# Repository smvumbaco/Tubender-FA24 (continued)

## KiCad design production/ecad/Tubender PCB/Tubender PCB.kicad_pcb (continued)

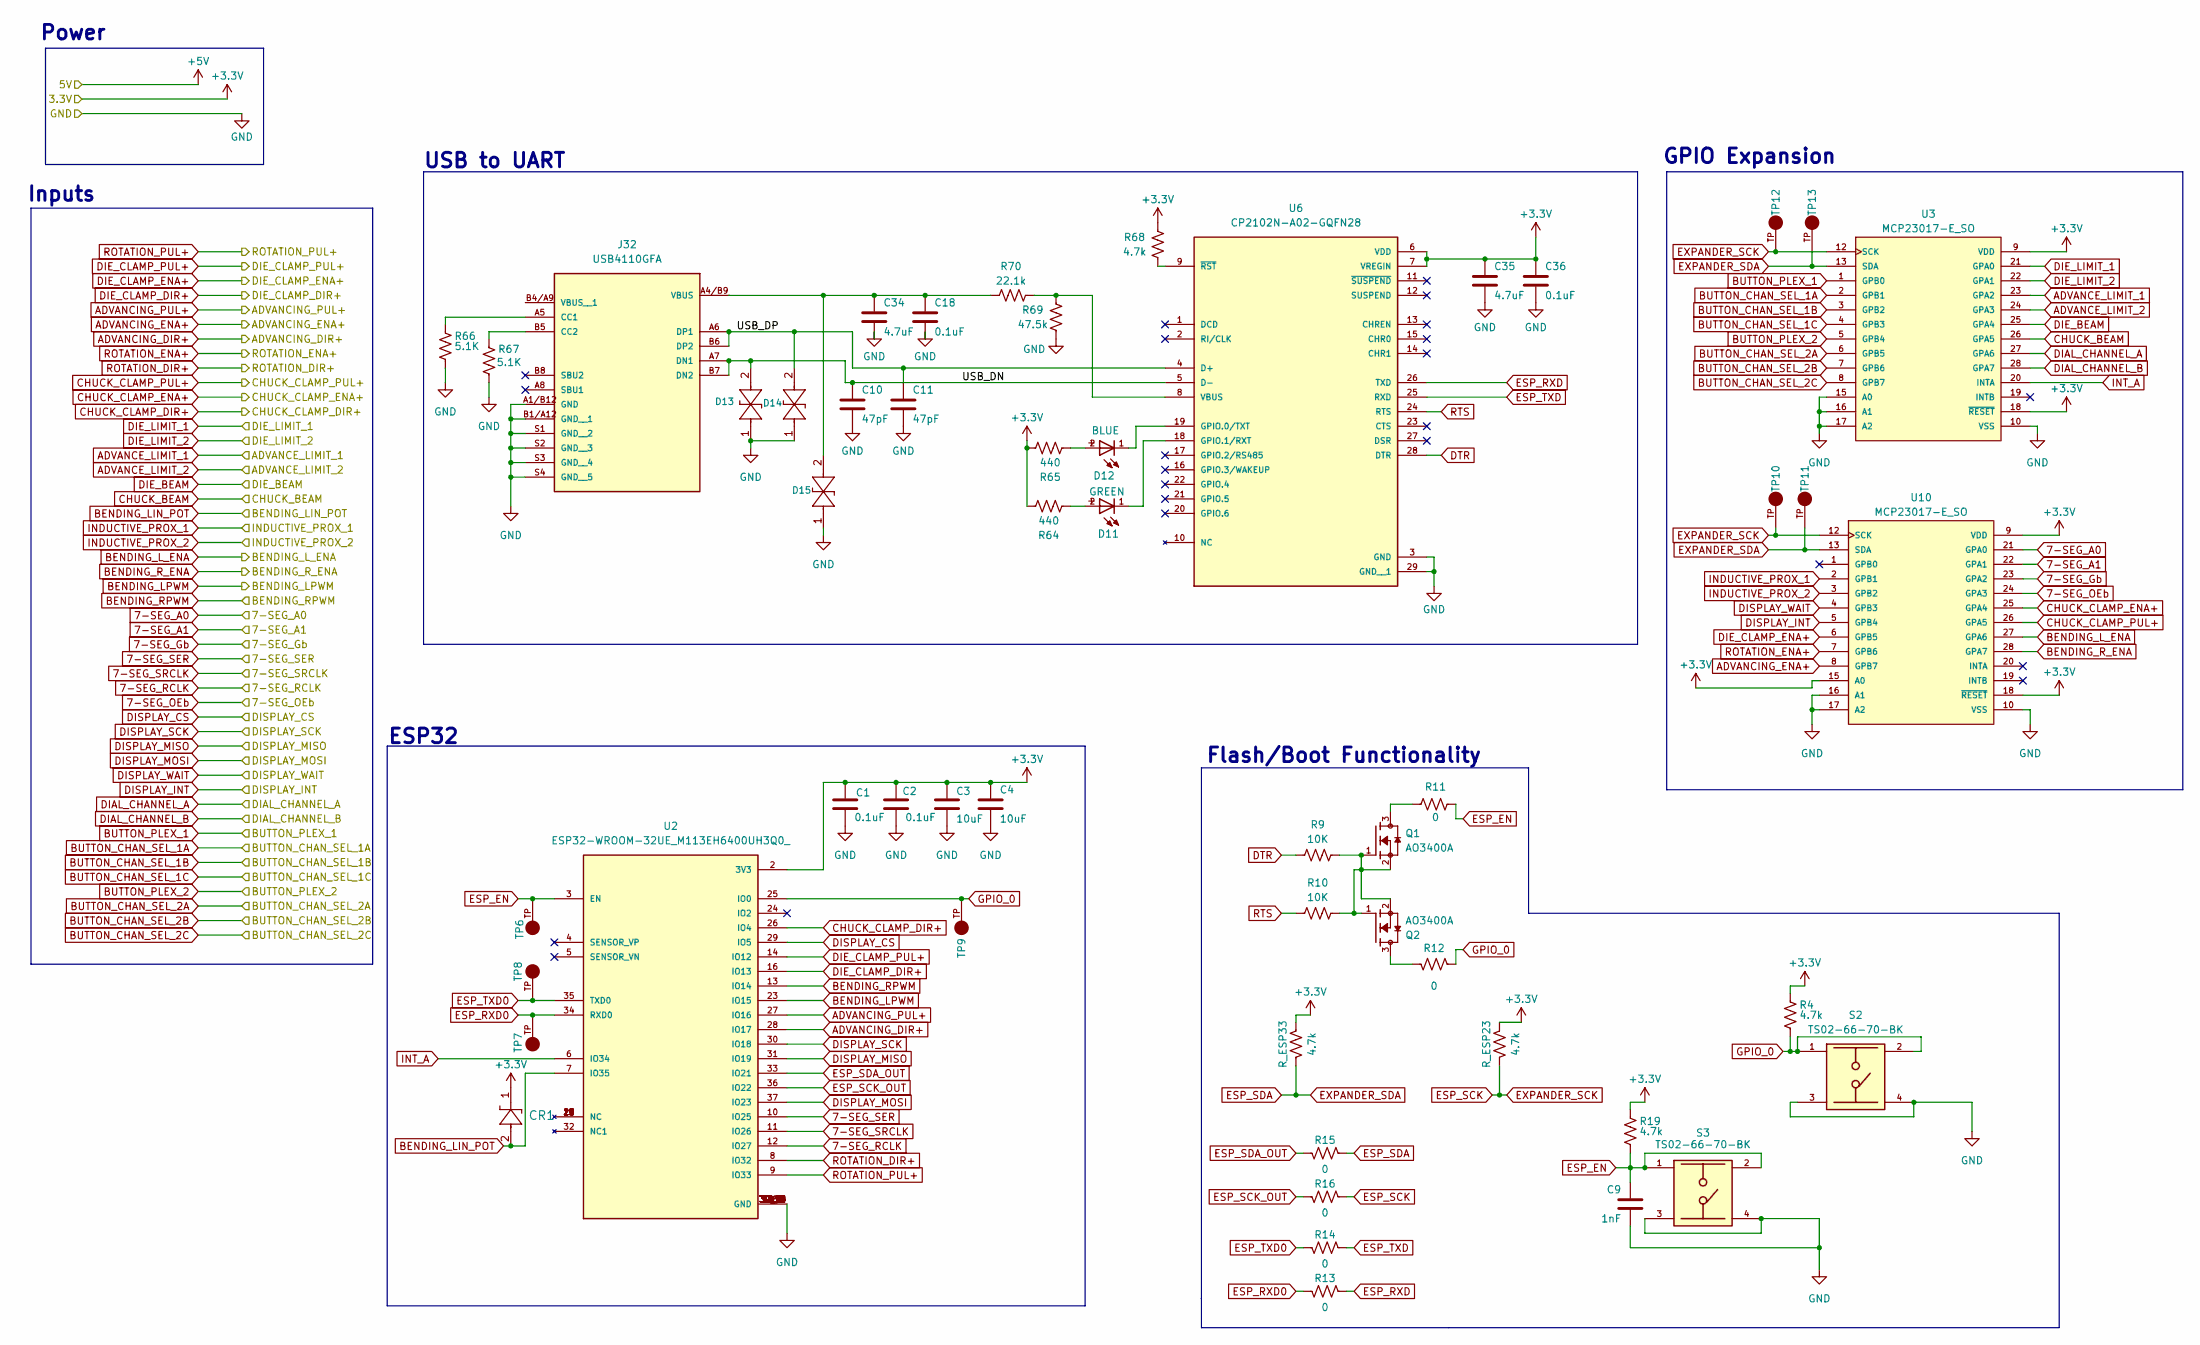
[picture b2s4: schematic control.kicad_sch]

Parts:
C1, C2, C18, C36: 0.1uF; C_0805_2012Metric
C3, C4: 10uF; C_0805_2012Metric
C9: 1nF; C_0805_2012Metric
C10, C11: 47pF; C_0805_2012Metric
C34, C35: 4.7uF; C_0805_2012Metric
CR1: PMEG4010CEH; SOD123F_NXP
D11: GREEN; WL-SMCW_0603
D12: BLUE; WL-SMCW_0603
D13, D14, D15: RCLAMP1521P.TCT; TVS_DFN2_SLP1006P2_SEM
J32: USB4110GFA; GCT_USB4110GFA
Q1, Q2: AO3400A; SOT95P280X125-3N; PARTREV L
R4, R19, R68: 4.7k; R_0805_2012Metric
R9, R10: 10K; R_0805_2012Metric
R11, R12, R13, R14, R15, R16: 0; R_0805_2012Metric
R64, R65: 440; R_0805_2012Metric
R66, R67: 5.1K; R_0805_2012Metric
R69: 47.5k; R_0805_2012Metric
R70: 22.1k; R_0805_2012Metric
R_ESP23, R_ESP33: 4.7k; R_0805_2012Metric
S2, S3: TS02-66-70-BK; SW_TS02-66-70-BK-260-LCR-D; PARTREV 1.0
TP6, TP7, TP8, TP9, TP10, TP11, TP12, TP13: 5006; KEYSTONE_5006; PARTREV F
U2: ESP32-WROOM-32UE_M113EH6400UH3Q0_; MODULE_ESP32-WROOM-32UE_M113EH6400UH3Q0_; PARTREV 1.2
U3, U10: MCP23017-E_SO; SOIC127P1030X265-28N; PARTREV C
U6: CP2102N-A02-GQFN28; QFN50P500X500X80-29N; PARTREV 1.5

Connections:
3.3V: C1.1, C2.1, C3.1, C4.1, C35.1, C36.1, CR1.1, R4.2, R19.2, R64.2, R65.2, R68.2, R_ESP23.2, R_ESP33.2, U2.2 (3V3), U3.9 (VDD), U3.18 (~RESET), U6.6 (VDD), U6.7 (VREGIN), U10.9 (VDD), U10.15 (A0), U10.18 (~RESET); also elsewhere on the board
7-SEG_A0: U10.21 (GPA0); also elsewhere on the board
7-SEG_A1: U10.22 (GPA1); also elsewhere on the board
7-SEG_Gb: U10.23 (GPA2); also elsewhere on the board
7-SEG_OEb: U10.24 (GPA3); also elsewhere on the board
7-SEG_RCLK: U2.12 (IO27); also elsewhere on the board
7-SEG_SER: U2.10 (IO25); also elsewhere on the board
7-SEG_SRCLK: U2.11 (IO26); also elsewhere on the board
/CONTROL/USB_DN: C10.1, D13.2, J32.A7 (DN1), J32.B7 (DN2), U6.5 (D-)
/CONTROL/USB_DP: C11.1, D14.2, J32.A6 (DP1), J32.B6 (DP2), U6.4 (D+)
ADVANCE_LIMIT_1: U3.23 (GPA2); also elsewhere on the board
ADVANCE_LIMIT_2: U3.24 (GPA3); also elsewhere on the board
ADVANCING_DIR+: U2.28 (IO17); also elsewhere on the board
ADVANCING_ENA+: U10.8 (GPB7); also elsewhere on the board
ADVANCING_PUL+: U2.27 (IO16); also elsewhere on the board
BENDING_LIN_POT: CR1.2, U2.7 (IO35); also elsewhere on the board
BENDING_LPWM: U2.23 (IO15); also elsewhere on the board
BENDING_L_ENA: U10.27 (GPA6); also elsewhere on the board
BENDING_RPWM: U2.13 (IO14); also elsewhere on the board
BENDING_R_ENA: U10.28 (GPA7); also elsewhere on the board
BUTTON_CHAN_SEL_1A: U3.2 (GPB1); also elsewhere on the board
BUTTON_CHAN_SEL_1B: U3.3 (GPB2); also elsewhere on the board
BUTTON_CHAN_SEL_1C: U3.4 (GPB3); also elsewhere on the board
BUTTON_CHAN_SEL_2A: U3.6 (GPB5); also elsewhere on the board
BUTTON_CHAN_SEL_2B: U3.7 (GPB6); also elsewhere on the board
BUTTON_CHAN_SEL_2C: U3.8 (GPB7); also elsewhere on the board
BUTTON_PLEX_1: U3.1 (GPB0); also elsewhere on the board
BUTTON_PLEX_2: U3.5 (GPB4); also elsewhere on the board
CHUCK_BEAM: U3.26 (GPA5); also elsewhere on the board
CHUCK_CLAMP_DIR+: U2.26 (IO4); also elsewhere on the board
CHUCK_CLAMP_ENA+: U10.25 (GPA4); also elsewhere on the board
CHUCK_CLAMP_PUL+: U10.26 (GPA5); also elsewhere on the board
DIAL_CHANNEL_A: U3.27 (GPA6); also elsewhere on the board
DIAL_CHANNEL_B: U3.28 (GPA7); also elsewhere on the board
DIE_BEAM: U3.25 (GPA4); also elsewhere on the board
DIE_CLAMP_DIR+: U2.16 (IO13); also elsewhere on the board
DIE_CLAMP_ENA+: U10.6 (GPB5); also elsewhere on the board
DIE_CLAMP_PUL+: U2.14 (IO12); also elsewhere on the board
DIE_LIMIT_1: U3.21 (GPA0); also elsewhere on the board
DIE_LIMIT_2: U3.22 (GPA1); also elsewhere on the board
DISPLAY_CS: U2.29 (IO5); also elsewhere on the board
DISPLAY_INT: U10.5 (GPB4); also elsewhere on the board
DISPLAY_MISO: U2.31 (IO19); also elsewhere on the board
DISPLAY_MOSI: U2.37 (IO23); also elsewhere on the board
DISPLAY_SCK: U2.30 (IO18); also elsewhere on the board
DISPLAY_WAIT: U10.4 (GPB3); also elsewhere on the board
DTR: R9.1, U6.28 (DTR)
ESP_EN: C9.1, R11.2, R19.1, S3.1, S3.2, TP6.TP, U2.3 (EN)
ESP_RXD: R13.2, U6.26 (TXD)
ESP_RXD0: R13.1, TP7.TP, U2.34 (RXD0)
ESP_SCK: R16.2, R_ESP23.1, TP10.TP, TP12.TP, U3.12 (SCK), U10.12 (SCK)
ESP_SCK_OUT: R16.1, U2.36 (IO22)
ESP_SDA: R15.2, R_ESP33.1, TP11.TP, TP13.TP, U3.13 (SDA), U10.13 (SDA)
ESP_SDA_OUT: R15.1, U2.33 (IO21)
ESP_TXD: R14.2, U6.25 (RXD)
ESP_TXD0: R14.1, TP8.TP, U2.35 (TXD0)
GND: C1.2, C2.2, C3.2, C4.2, C9.2, C10.2, C11.2, C18.2, C34.2, C35.2, C36.2, D13.1, D14.1, D15.1, J32.A1/B12 (GND), J32.B1/A12 (GND__1), J32.S1 (GND__2), J32.S2 (GND__3), J32.S3 (GND__4), J32.S4 (GND__5), R66.1, R67.1, R69.1, S2.3, S2.4, S3.3, S3.4, U2.1 (GND), U2.15 (GND), U2.38 (GND), U2.39_1 (GND), U2.39_2 (GND), U2.39_3 (GND), U2.39_4 (GND), U2.39_5 (GND), U2.39_6 (GND), U2.39_7 (GND), U2.39_8 (GND), U2.39_9 (GND), U2.39_10 (GND), U2.39_11 (GND), U2.39_12 (GND), U2.39_13 (GND), U2.39_14 (GND), U2.39_15 (GND), U2.39_16 (GND), U2.39_17 (GND), U2.39_18 (GND), U2.39_19 (GND), U2.39_20 (GND), U2.39_21 (GND), U3.10 (VSS), U3.15 (A0), U3.16 (A1), U3.17 (A2), U6.3 (GND), U6.29 (GND__1), U10.10 (VSS), U10.16 (A1), U10.17 (A2); also elsewhere on the board
GPIO_0: R4.1, R12.2, S2.1, S2.2, TP9.TP, U2.25 (IO0)
INDUCTIVE_PROX_1: U10.2 (GPB1); also elsewhere on the board
INDUCTIVE_PROX_2: U10.3 (GPB2); also elsewhere on the board
INT_A: U2.6 (IO34), U3.20 (INTA)
unnamed: D11.2, R64.1
unnamed: D12.2, R65.1
unnamed: J32.A5 (CC1), R66.2
unnamed: J32.B5 (CC2), R67.2
unnamed: C18.1, C34.1, D15.2, J32.A4/B9 (VBUS), R70.1
unnamed: Q1.1, Q1.2, Q2.1, Q2.2, R9.2, R10.2
unnamed: Q1.3, R11.1
unnamed: Q2.3, R12.1
unnamed: D12.1, U6.19 (GPIO.0/TXT)
unnamed: D11.1, U6.18 (GPIO.1/RXT)
unnamed: R69.2, R70.2, U6.8 (VBUS)
unnamed: R68.1, U6.9 (~RST)
ROTATION_DIR+: U2.8 (IO32); also elsewhere on the board
ROTATION_ENA+: U10.7 (GPB6); also elsewhere on the board
ROTATION_PUL+: U2.9 (IO33); also elsewhere on the board
RTS: R10.1, U6.24 (RTS)

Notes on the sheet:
USB to UART
GPIO Expansion
Inputs
ESP32
Power
Flash/Boot Functionality

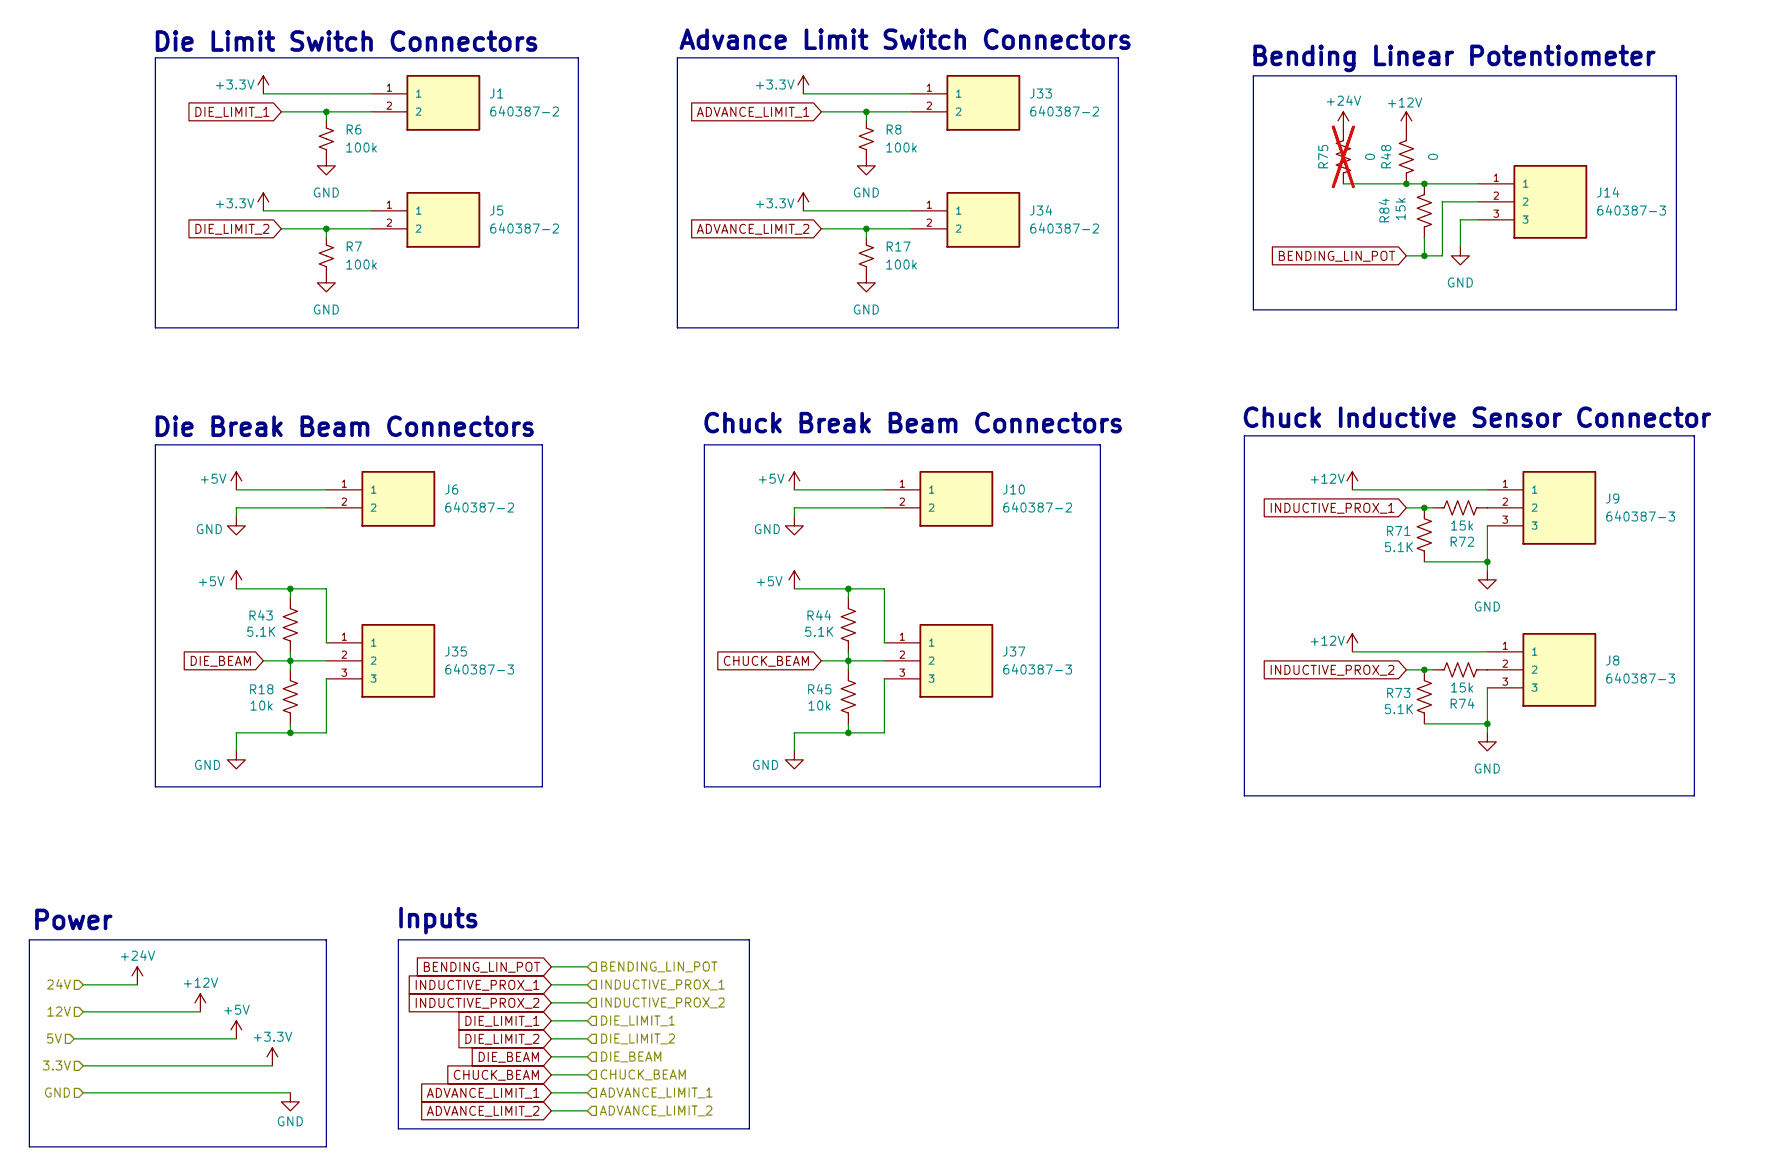
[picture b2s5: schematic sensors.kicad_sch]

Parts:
J1, J5, J6, J10, J33, J34: 640387-2; TE_640387-2; PARTREV R
J8, J9, J14, J35, J37: 640387-3; TE_640387-3; PARTREV R
R6, R7, R8, R17: 100k; R_0805_2012Metric
R18, R45: 10k; R_0805_2012Metric
R43, R44, R71, R73: 5.1K; R_0805_2012Metric
R48: 0; R_0805_2012Metric
R72, R74, R84: 15k; R_0805_2012Metric
R75: 0; R_0805_2012Metric; not fitted

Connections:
3.3V: J1.1, J5.1, J33.1, J34.1; also elsewhere on the board
5V: J6.1, J10.1, J35.1, J37.1, R43.2, R44.2; also elsewhere on the board
12V: J8.1, J9.1, R48.2; also elsewhere on the board
24V: R75.2; also elsewhere on the board
ADVANCE_LIMIT_1: J33.2, R8.2; also elsewhere on the board
ADVANCE_LIMIT_2: J34.2, R17.2; also elsewhere on the board
BENDING_LIN_POT: J14.2, R84.1; also elsewhere on the board
CHUCK_BEAM: J37.2, R44.1, R45.2; also elsewhere on the board
DIE_BEAM: J35.2, R18.2, R43.1; also elsewhere on the board
DIE_LIMIT_1: J1.2, R6.2; also elsewhere on the board
DIE_LIMIT_2: J5.2, R7.2; also elsewhere on the board
GND: J6.2, J8.3, J9.3, J10.2, J14.3, J35.3, J37.3, R6.1, R7.1, R8.1, R17.1, R18.1, R45.1, R71.1, R73.1; also elsewhere on the board
INDUCTIVE_PROX_1: R71.2, R72.2; also elsewhere on the board
INDUCTIVE_PROX_2: R73.2, R74.2; also elsewhere on the board
unnamed: J8.2, R74.1
unnamed: J9.2, R72.1
unnamed: J14.1, R48.1, R75.1, R84.2

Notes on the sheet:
Chuck Inductive Sensor Connector
Advance Limit Switch Connectors
Die Break Beam Connectors
Power
Inputs
Chuck Break Beam Connectors
Bending Linear Potentiometer
Die Limit Switch Connectors

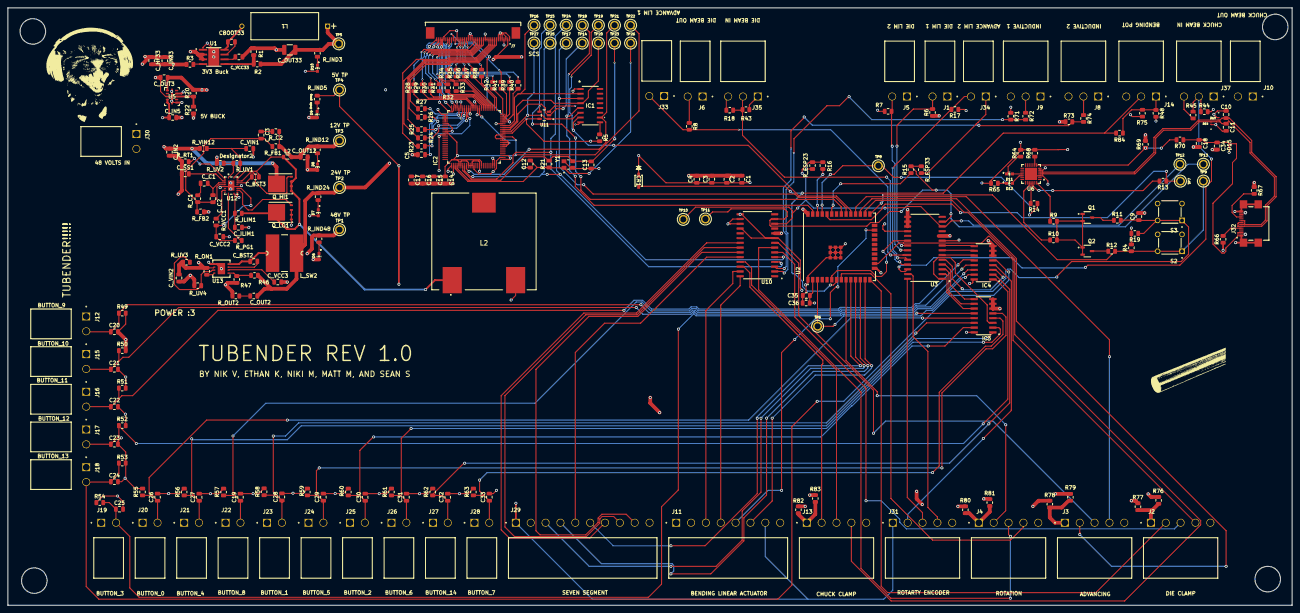
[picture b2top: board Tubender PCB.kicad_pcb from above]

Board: 4 copper layers, 342.4 x 159.2 mm, 258 parts (0 on the bottom side), 193 nets.

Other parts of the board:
L2#2: 12uH; L_0805_2012Metric

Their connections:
12V: L2#2.2; also elsewhere on the board
unnamed 141: L2#2.1; also elsewhere on the board

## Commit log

2024-09-12 Tubebender KiCAD File Upload
    Blank KiCAD with Hierarchical Pages Created
2024-09-17 added name on power sheet
2024-09-18 initial niki push
2024-09-18 Added TItle
2024-09-18 Matt Commit Message
2024-09-22 Add microcontroller schematic
2024-09-22 added 3.3V buck IC symbol and changed power sheet directory
2024-09-22 sorry same commit but i forgot some stuff
2024-09-26 just test push!
2024-09-29 added power page
2024-09-29 small changes to names in 3V3 schematic
2024-09-29 Added 3V3 buck circuitry to main branch, added 3V3 label
2024-09-29 3V3 output cap value change based on phase margin
2024-10-01 Add microcontroller to control schematic
2024-10-02 First MCU Edit
2024-10-03 MCU and such
2024-10-03 More MCU Stuff
2024-10-03 MCU Rev1 Complete
2024-10-03 Added Motor Connectors
2024-10-03 Fixed a Switch or 2
2024-10-06 Add UI sheet
2024-10-06 Add UI sheet sections
2024-10-07 Added IC and some connections for 12V buck. Added 12V output connection
2024-10-07 Added Prox Sensor Nets
2024-10-08 All passives valued for 12V buck
2024-10-08 Add buck converter datasheets
2024-10-08 Add 5V 20mA buck, symbol, footprint, and datasheet
2024-10-09 Motor Page
2024-10-09 add box to identify 12V and 5V buck
2024-10-09 8 connector
2024-10-09 names and stuff
2024-10-09 GRRR deleted old files
2024-10-09 sensor connectors - niki
2024-10-09 STATUS LEDS!!!
2024-10-09 sensors!
2024-10-10 adding 3pin connector
2024-10-10 Added UI components, shift registers, and mux
2024-10-10 add UI components
2024-10-10 Temp page added
2024-10-11 7 Segment, Buttons, Plexers Oh MY!
2024-10-11 Driver pin out
2024-10-11 Yay, more components!
    Buffer and Crystal
2024-10-11 More driver pins yay
2024-10-11 Formatting
    Boom
2024-10-11 24V Buck Said WHOOO?!
2024-10-11 Completed RA8875 Driver
2024-10-11 adjustments
2024-10-11 final for rev 1
2024-10-11 Display to MCU
    Forgot to add global nets for display to the control page, my b
2024-10-11 Fixed Button Connectors
    All done! Enjoy :)
2024-10-12 Fixed 12V buck and power LEDs
2024-10-14 Moved Display SPI to MCU VSPI and Organized UI Sheet
2024-10-15 Separated into Two PCBS
    UI and Main now seperated
2024-10-15 Fixed the Nets
2024-10-16 Fixing Sheets, 1 Board Again
2024-10-16 Adding Test Points
2024-10-16 Change input labels to outputs
2024-10-16 Make 2nd Board
2024-10-16 Reorganized UI
2024-10-16 Again try
2024-10-16 errrmskt, what the sigma?
2024-10-16 Fix it?
2024-10-16 Replace outdated shift register
2024-10-16 Fixing output/input markers
2024-10-16 Layout File Made
2024-10-16 UI Board Fully Separated Now
2024-10-16 Flashing and Buttons
    Moved to a more proven way to flash ESP's and also made all the buttons pull ups instead of pull downs.
2024-10-17 Just tinkering with Nets
2024-10-17 annotate schematic
2024-10-17 start power layout
2024-10-17 Replaced MUX IC and connected touch functionality pins
2024-10-18 layed out most buck architectures, one status led
2024-10-20 unsure update
2024-10-20 Added Testpoints to UI sheet
2024-10-20 pcb changes
2024-10-20 GITHUB IS NOT MY FRIEND
2024-10-21 Power mostly complete
2024-10-21 quick pcb edit
2024-10-22 sensor updates!
2024-10-22 connected one line on 5V Buck
2024-10-23 trying to fix trace issue
2024-10-23 starting to layout non-power stuff
2024-10-23 Added Footprints
2024-10-23 more changes
2024-10-23 working on mcu layout
2024-10-23 More FootyPrints
2024-10-23 a few lines here and there
2024-10-23 LCK file get out
2024-10-24 added some traces
2024-10-25 small change, removed one trace
2024-10-25 Added SD card reader
2024-10-26 Some intial work for rotary encoder on PCB
2024-10-27 more traces
2024-10-28 lots of traces complete, USB-UART pretty much complete and flash/boot functionality pretty much complete
2024-10-29 Added UI footprints and first draft of layout
2024-10-29 Added SD Connector to UI PCB
2024-10-30 ADDED POWER AND GROUND PLANE AND DID MORE TRACES
2024-10-30 almost done
2024-10-31 minor changes and vias
2024-10-31 0 Ohm Resistors
    Added DNP 0 Ohm's connected to the 24V rail to the motor connectors power out pin. This is in case we have issues with the drivers taking 48 volts and to just have flexbility
2024-10-31 Layout for 0 Ohm Resistors
2024-10-31 Fixed MCU Pinout Schematic
2024-10-31 More MCU Updates
2024-10-31 Updated Layout for new MCU Connections
2024-10-31 Added Display Daughter Board PCB and start UI layout
2024-10-31 Differential Pairs
2024-10-31 small changes and reducing errors
2024-10-31 Finished First Draft Layout of UI PCB
2024-11-01 Potentiometer Update
2024-11-02 got rid of all drc issues
2024-11-03 quick push with diode
2024-11-03 final connectors!
2024-11-03 lfg!!!
2024-11-04 Fixed RC Cap Value
2024-11-04 cat?
2024-11-04 Duplicate Connectors on Main PCB
2024-11-04 Resolved DRC Erros on connector board
2024-11-04 quick changes
2024-11-04 sorry ignore me
2024-11-04 Revert "sorry ignore me"
    This reverts commit 73c02b3aeddfc779c4a0e0557f647e9a66e19b2e.
2024-11-04 Revert "okay"
    This reverts commit a5d04aacf17b2a0e1fddfefa2daa114170fce467, reversing
    changes made to 85b8c41c143529192f5821f916a37eef7153b122.
2024-11-04 Revert "quick changes"
    This reverts commit 85b8c41c143529192f5821f916a37eef7153b122.
2024-11-04 Fixed Blind Vias
2024-11-04 fixed some vias and edited 3v3 line
2024-11-04 Fixed DRC issues with UI board and added mounting holes
2024-11-05 Fixed daughter board DRC issues
2024-11-05 More Updates
2024-11-05 Added GND pours to all 4 layers
2024-11-05 switched inductors and 100uF cap:
2024-11-05 Revert "Added GND pours to all 4 layers"
    This reverts commit a877a5ca7bb4c7270d5b11e79493b0bc4f3f0860.
2024-11-05 Reapply "Added GND pours to all 4 layers"
    This reverts commit 46062e0e4605256fedf6ce9486694907de27c252.
2024-11-05 please let me merge
2024-11-06 replaced and rewired IC2
2024-11-06 DRC and INTA
    Fixed the final DRC issue and also attached the interupt pin from the expander with lots of our sensors to the ESP
2024-11-06 moved some silkscreens
2024-11-06 Added GND pours to all planes and a crap ton of GND vias
2024-11-07 Fixed 12v Trace Width
2024-11-07 More Fix
2024-11-07 new datasheet
2024-11-14 added step files for all components and full pcb
2024-11-20 Added STEP files for UI board
